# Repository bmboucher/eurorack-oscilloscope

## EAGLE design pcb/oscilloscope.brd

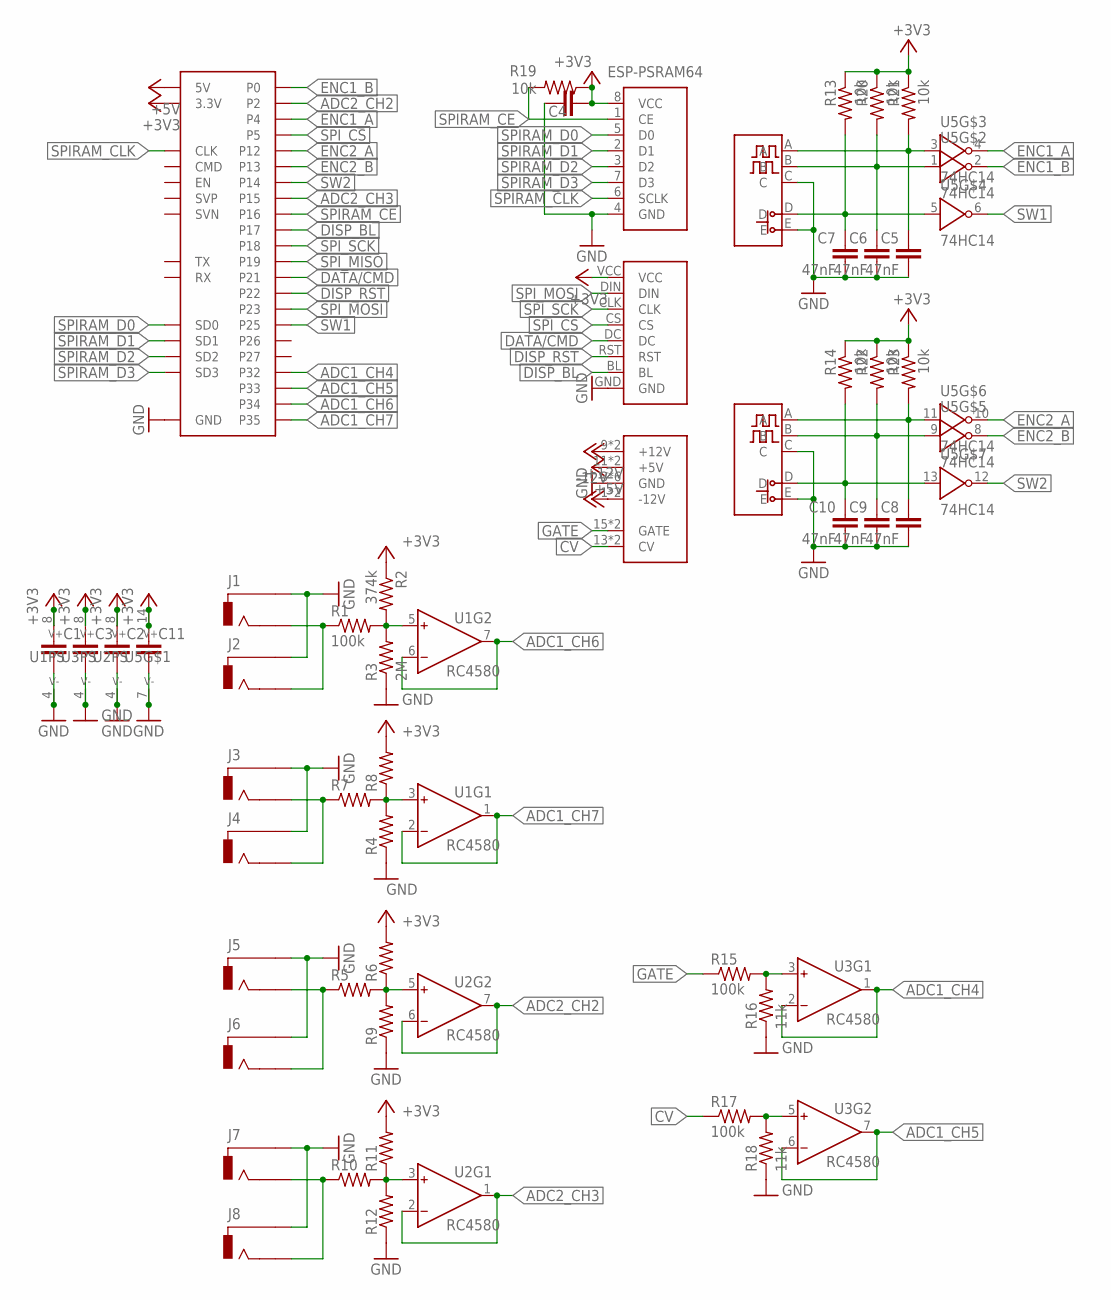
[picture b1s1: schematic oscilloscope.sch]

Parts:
C1, C2, C3, C4, C11: C-EUC0805; C0805
C5, C6, C7, C8, C9, C10: 47nF; C0805
DS1: ST27789_DISPLAY; ST7789_DISPLAY
J1, J2, J3, J4, J5, J6, J7, J8: 35PM1
M1: ESP32
R1, R15, R17: 100k; R0805
R2: 374k; R0805
R3: 2M; R0805
R4, R5, R6, R7, R8, R9, R10, R11, R12: R-US_R0805; R0805
R13, R14, R19, R20, R21, R22, R23: 10k; R0805
R16, R18: 11k; R0805
SW1, SW2: EN12-HS
U1, U2, U3: RC4580; SOIC-8
U4: ESP-PSRAM64; SOIC-8
U5: 74HC14; SOIC127P600X175-14N
U$1: EURORACK; 302-S161

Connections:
+3V3: C1.1, C2.1, C3.1, C4.2, C11.1, DS1.VCC, M1.X0 (3.3V), R2.1, R6.2, R8.2, R11.2, R13.1, R14.1, R19.1, R20.1, R21.1, R22.1, R23.1, U1.8 (V+), U2.8 (V+), U3.8 (V+), U4.8 (VCC), U5.14 (V+)
+5V: M1.X18 (5V), U$1.11 (+5V), U$1.12 (+5V)
+12V: U$1.9 (+12V), U$1.10 (+12V)
-12V: U$1.1 (-12V), U$1.2 (-12V)
ADC1_CH4: M1.X6 (P32), U3.1 (OUT), U3.2 (IN-)
ADC1_CH5: M1.X7 (P33), U3.6 (IN-), U3.7 (OUT)
ADC1_CH6: M1.X4 (P34), U1.6 (IN-), U1.7 (OUT)
ADC1_CH7: M1.X5 (P35), U1.1 (OUT), U1.2 (IN-)
ADC2_CH2: M1.X23 (P2), U2.6 (IN-), U2.7 (OUT)
ADC2_CH3: M1.X22 (P15), U2.1 (OUT), U2.2 (IN-)
CV: R17.1, U$1.13 (CV), U$1.14 (CV)
DATA/CMD: DS1.DC, M1.X32 (P21)
DISP_BL: DS1.BL, M1.X27 (P17)
DISP_RST: DS1.RST, M1.X35 (P22)
ENC1_A: M1.X25 (P4), U5.4 (O)
ENC1_A_I: C5.1, R21.2, SW1.A, U5.3 (I)
ENC1_B: M1.X24 (P0), U5.2 (O)
ENC1_B_I: C6.1, R20.2, SW1.B, U5.1 (I)
ENC2_A: M1.X12 (P12), U5.10 (O)
ENC2_A_I: C8.1, R23.2, SW2.A, U5.11 (I)
ENC2_B: M1.X14 (P13), U5.8 (O)
ENC2_B_I: C9.1, R22.2, SW2.B, U5.9 (I)
GATE: R15.1, U$1.15 (GATE), U$1.16 (GATE)
GND: C1.2, C2.2, C3.2, C4.1, C5.2, C6.2, C7.2, C8.2, C9.2, C10.2, C11.2, DS1.GND, J1.SLEEVE, J2.SLEEVE, J3.SLEEVE, J4.SLEEVE, J5.SLEEVE, J6.SLEEVE, J7.SLEEVE, J8.SLEEVE, M1.X13 (GND), M1.X31 (GND), M1.X37 (GND), R3.1, R4.1, R9.1, R12.1, R16.1, R18.1, SW1.C, SW1.E, SW2.C, SW2.E, U1.4 (V-), U2.4 (V-), U3.4 (V-), U4.4 (GND), U5.7 (V-), U$1.3 (GND), U$1.4 (GND), U$1.5 (GND), U$1.6 (GND), U$1.7 (GND), U$1.8 (GND)
unnamed: R1.2, R2.2, R3.2, U1.5 (IN+)
unnamed: J1.TIP, J2.TIP, R1.1
unnamed: J3.TIP, J4.TIP, R7.1
unnamed: R5.2, R6.1, R9.2, U2.5 (IN+)
unnamed: J5.TIP, J6.TIP, R5.1
unnamed: R4.2, R7.2, R8.1, U1.3 (IN+)
unnamed: R10.2, R11.1, R12.2, U2.3 (IN+)
unnamed: J7.TIP, J8.TIP, R10.1
unnamed: R15.2, R16.2, U3.3 (IN+)
unnamed: R17.2, R18.2, U3.5 (IN+)
SPIRAM_CE: M1.X26 (P16), R19.2, U4.1 (CE)
SPIRAM_CLK: M1.X19 (CLK), U4.6 (SCLK)
SPIRAM_D0: M1.X20 (SD0), U4.5 (D0)
SPIRAM_D1: M1.X21 (SD1), U4.2 (D1)
SPIRAM_D2: M1.X15 (SD2), U4.3 (D2)
SPIRAM_D3: M1.X16 (SD3), U4.7 (D3)
SPI_CS: DS1.CS, M1.X28 (P5)
SPI_MISO: M1.X30 (P19)
SPI_MOSI: DS1.DIN, M1.X36 (P23)
SPI_SCK: DS1.CLK, M1.X29 (P18)
SW1: M1.X8 (P25), U5.6 (O)
SW1_I: C7.1, R13.2, SW1.D, U5.5 (I)
SW2: M1.X11 (P14), U5.12 (O)
SW2_I: C10.1, R14.2, SW2.D, U5.13 (I)

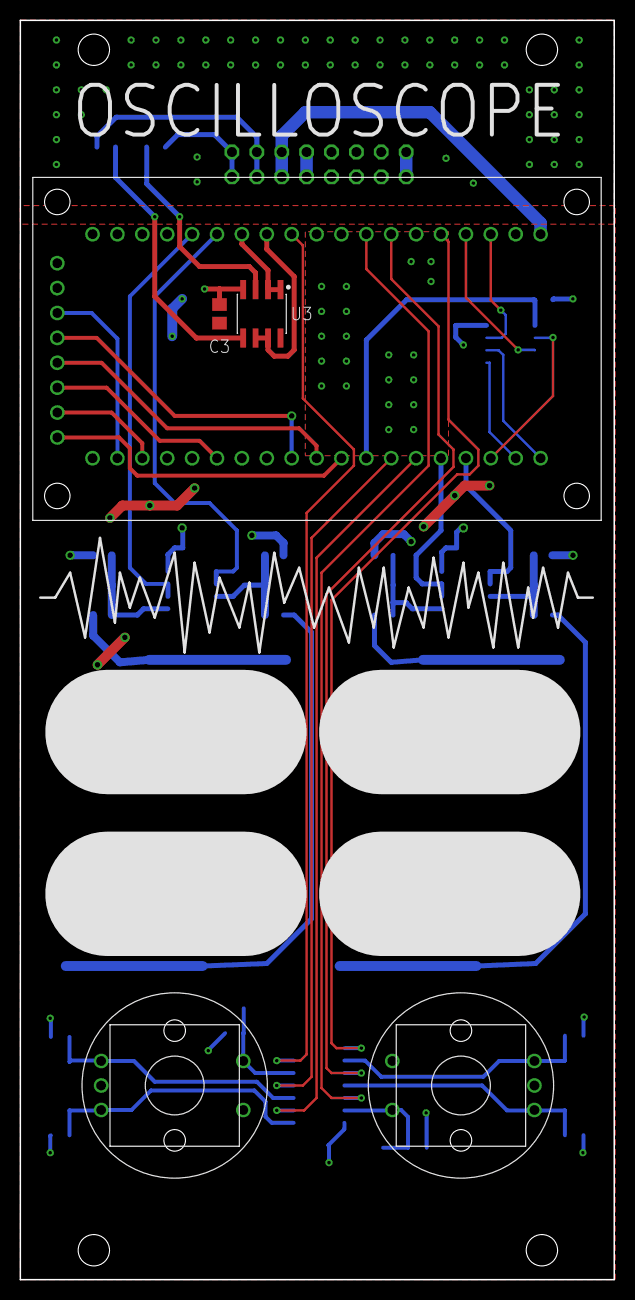
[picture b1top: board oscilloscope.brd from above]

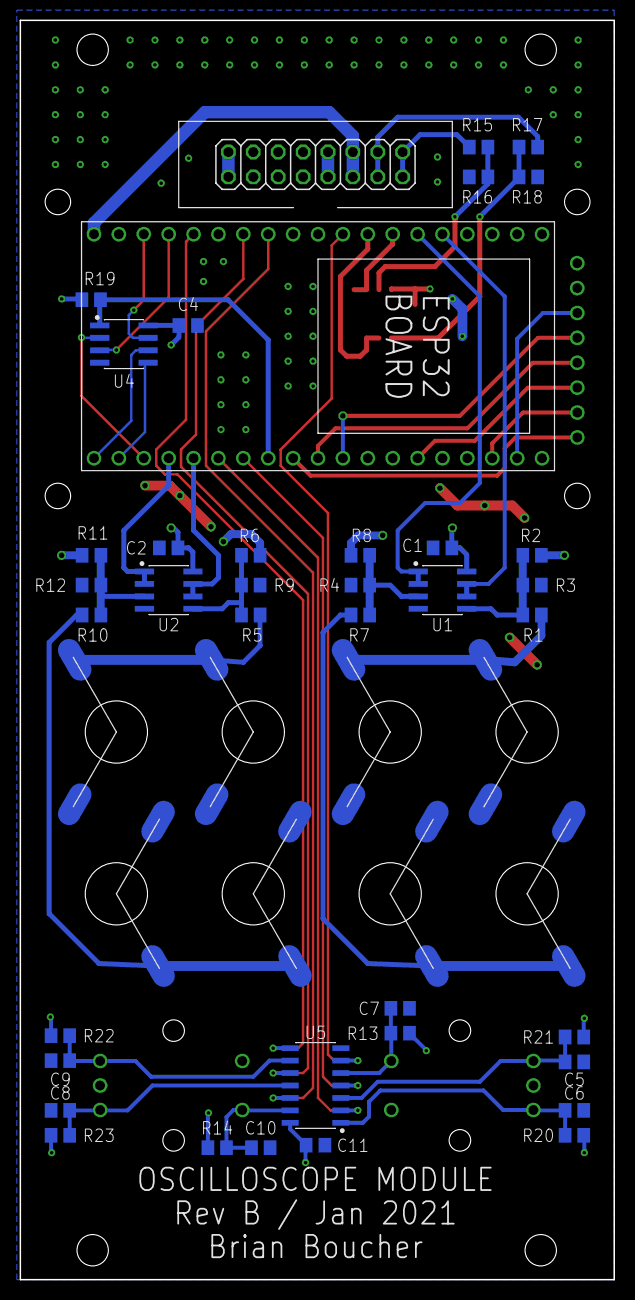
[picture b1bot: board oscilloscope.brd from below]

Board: 2 copper layers, 60.6 x 128.5 mm, 52 parts (39 on the bottom side), 47 nets.

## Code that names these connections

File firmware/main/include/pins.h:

#pragma once

// Rotary encoder 1
#define SW1 0
#define ENC1_A 16
#define ENC1_B 4

// Rotary encoder 2
#define SW2 14
#define ENC2_A 13
#define ENC2_B 12

// ST7789 display
#define ST7789_BCKL 17
#define ST7789_DC 21
#define ST7789_RST 22
#define ST7789_SPI_CS 5
#define ST7789_SPI_SCK 18
#define ST7789_SPI_MOSI 23
#define ST7789_SPI_MISO 19

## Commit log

2021-01-07 Initial commit - firmware
2021-01-07 Initial commit - PCB
2021-01-07 Updating VSCode project structure
2021-01-07 Fixing compile error in ST7789.c
2021-01-07 Updating to include ST7789.h file in VSCode
2021-01-20 Updating PCB to rev B
2021-01-20 Updating firmware 1-20
2021-01-20 Updating VSCode settings
